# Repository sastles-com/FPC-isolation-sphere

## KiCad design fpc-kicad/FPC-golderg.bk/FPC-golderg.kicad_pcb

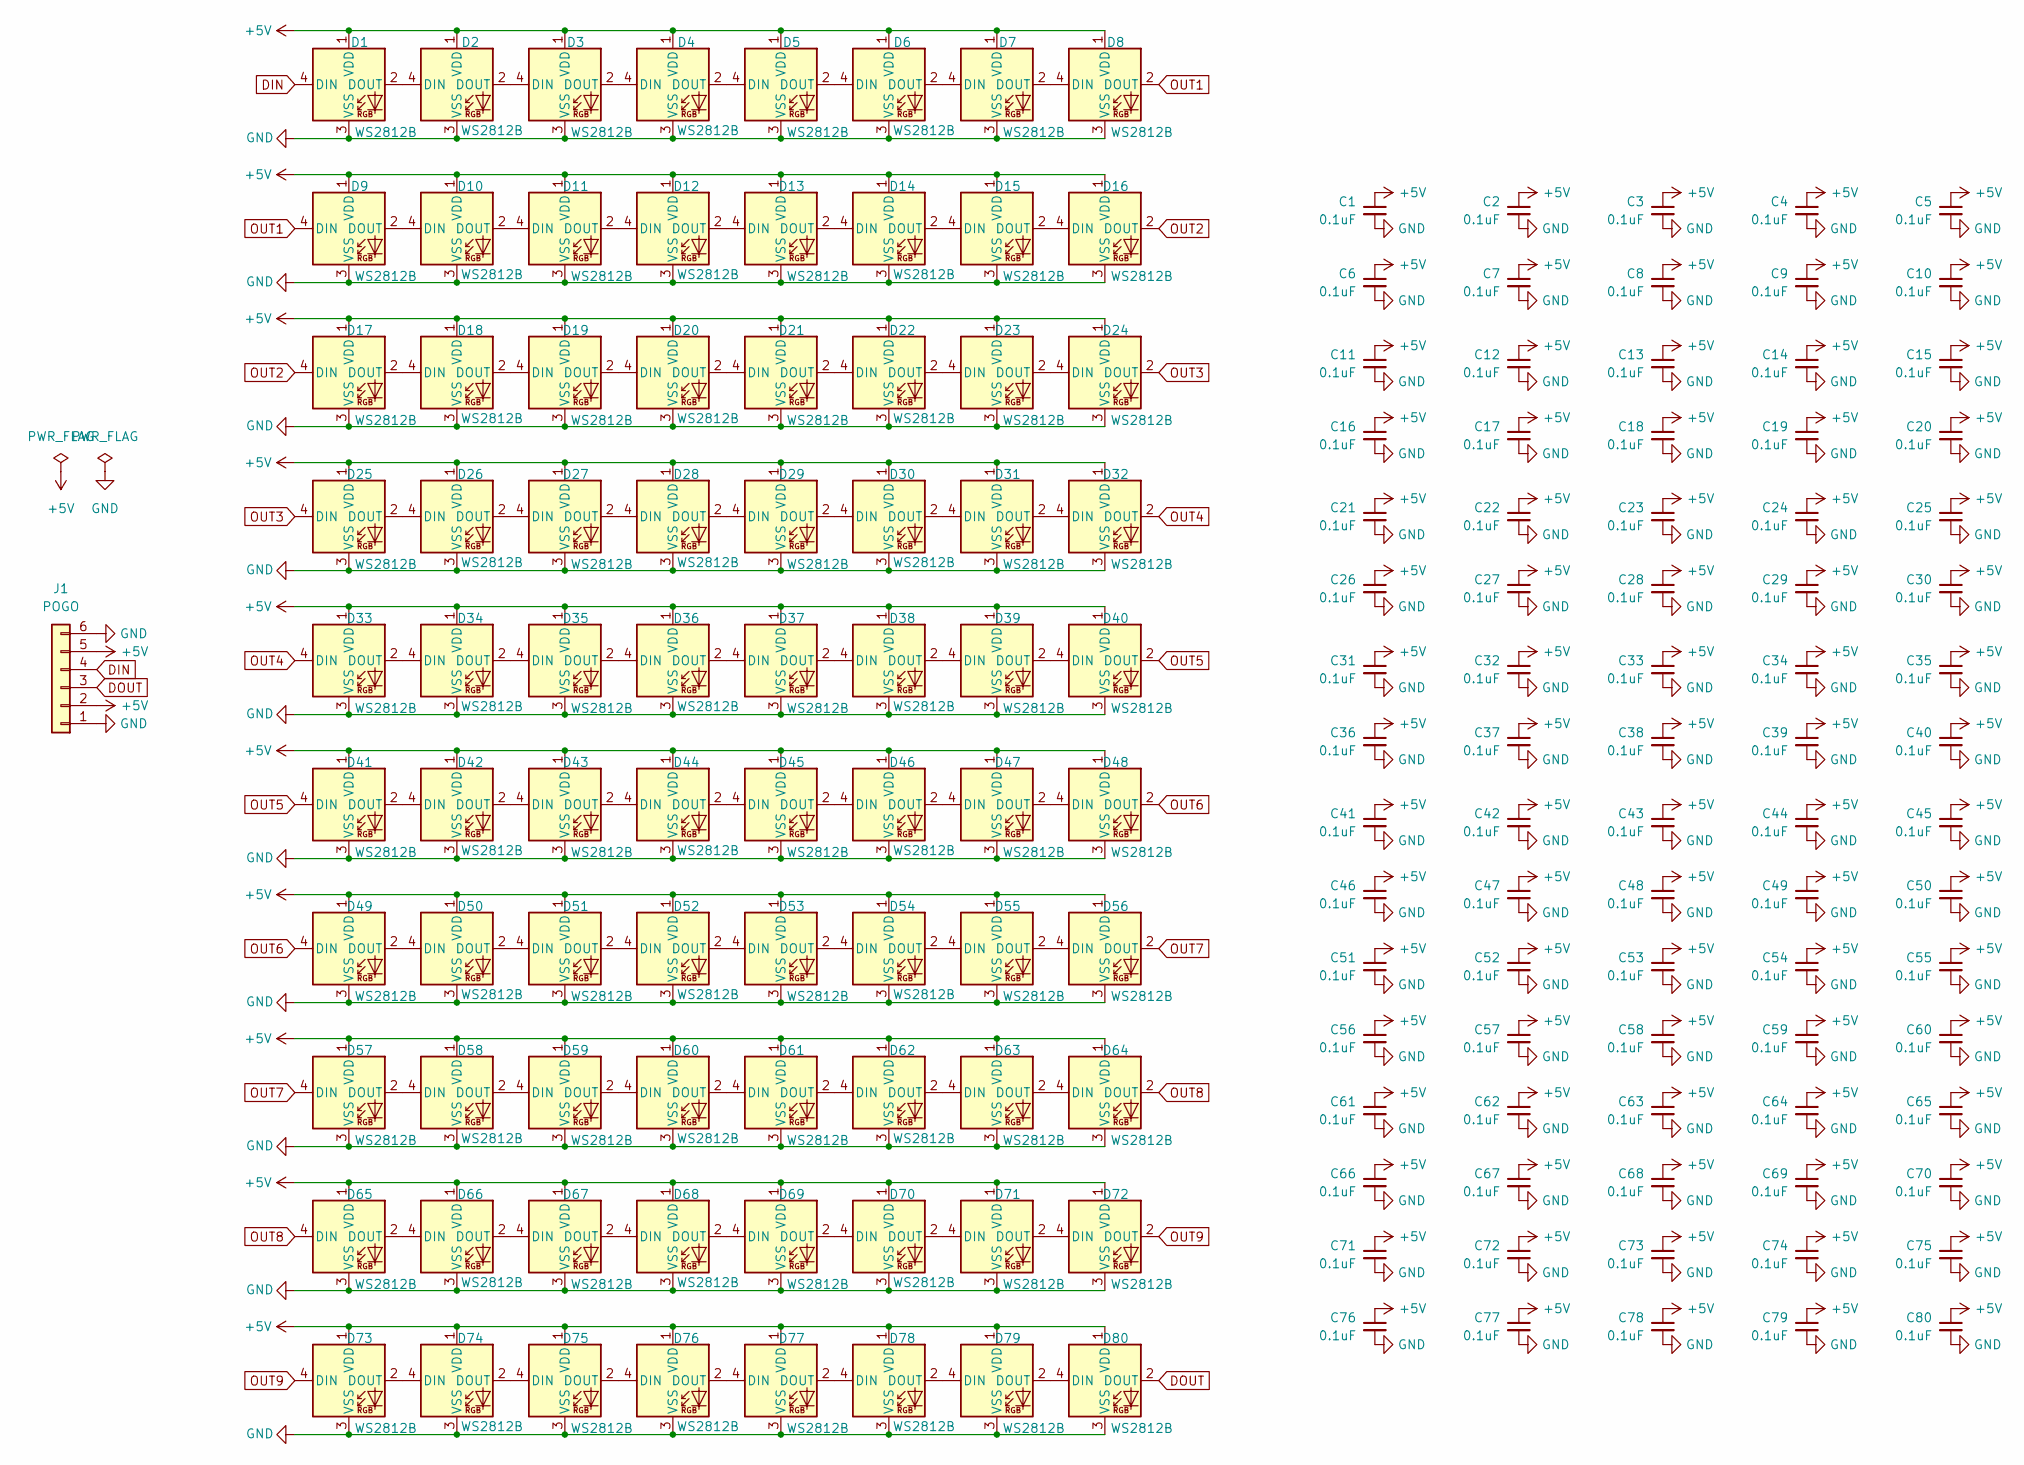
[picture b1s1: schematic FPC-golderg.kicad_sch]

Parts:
C1, C2, C3, C4, C5, C6, C7, C8, C9, C10, C11, C12, C13, C14, C15, C16, C17, C18, C19, C20, C21, C22, C23, C24, C25, C26, C27, C28, C29, C30, C31, C32, C33, C34, C35, C36, C37, C38, C39, C40, C41, C42, C43, C44, C45, C46, C47, C48, C49, C50, C51, C52, C53, C54, C55, C56, C57, C58, C59, C60, C61, C62, C63, C64, C65, C66, C67, C68, C69, C70, C71, C72, C73, C74, C75, C76, C77, C78, C79, C80: 0.1uF; C_0603_1608Metric
D1, D2, D3, D4, D5, D6, D7, D8, D9, D10, D11, D12, D13, D14, D15, D16, D17, D18, D19, D20, D21, D22, D23, D24, D25, D26, D27, D28, D29, D30, D31, D32, D33, D34, D35, D36, D37, D38, D39, D40, D41, D42, D43, D44, D45, D46, D47, D48, D49, D50, D51, D52, D53, D54, D55, D56, D57, D58, D59, D60, D61, D62, D63, D64, D65, D66, D67, D68, D69, D70, D71, D72, D73, D74, D75, D76, D77, D78, D79, D80: WS2812B; WS2812C-2020-nocut
J1: POGO; PinHeader_1x06_P2.54mm_Vertical

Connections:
+5V: C1.1, C2.1, C3.1, C4.1, C5.1, C6.1, C7.1, C8.1, C9.1, C10.1, C11.1, C12.1, C13.1, C14.1, C15.1, C16.1, C17.1, C18.1, C19.1, C20.1, C21.1, C22.1, C23.1, C24.1, C25.1, C26.1, C27.1, C28.1, C29.1, C30.1, C31.1, C32.1, C33.1, C34.1, C35.1, C36.1, C37.1, C38.1, C39.1, C40.1, C41.1, C42.1, C43.1, C44.1, C45.1, C46.1, C47.1, C48.1, C49.1, C50.1, C51.1, C52.1, C53.1, C54.1, C55.1, C56.1, C57.1, C58.1, C59.1, C60.1, C61.1, C62.1, C63.1, C64.1, C65.1, C66.1, C67.1, C68.1, C69.1, C70.1, C71.1, C72.1, C73.1, C74.1, C75.1, C76.1, C77.1, C78.1, C79.1, C80.1, D1.1 (VDD), D2.1 (VDD), D3.1 (VDD), D4.1 (VDD), D5.1 (VDD), D6.1 (VDD), D7.1 (VDD), D8.1 (VDD), D9.1 (VDD), D10.1 (VDD), D11.1 (VDD), D12.1 (VDD), D13.1 (VDD), D14.1 (VDD), D15.1 (VDD), D16.1 (VDD), D17.1 (VDD), D18.1 (VDD), D19.1 (VDD), D20.1 (VDD), D21.1 (VDD), D22.1 (VDD), D23.1 (VDD), D24.1 (VDD), D25.1 (VDD), D26.1 (VDD), D27.1 (VDD), D28.1 (VDD), D29.1 (VDD), D30.1 (VDD), D31.1 (VDD), D32.1 (VDD), D33.1 (VDD), D34.1 (VDD), D35.1 (VDD), D36.1 (VDD), D37.1 (VDD), D38.1 (VDD), D39.1 (VDD), D40.1 (VDD), D41.1 (VDD), D42.1 (VDD), D43.1 (VDD), D44.1 (VDD), D45.1 (VDD), D46.1 (VDD), D47.1 (VDD), D48.1 (VDD), D49.1 (VDD), D50.1 (VDD), D51.1 (VDD), D52.1 (VDD), D53.1 (VDD), D54.1 (VDD), D55.1 (VDD), D56.1 (VDD), D57.1 (VDD), D58.1 (VDD), D59.1 (VDD), D60.1 (VDD), D61.1 (VDD), D62.1 (VDD), D63.1 (VDD), D64.1 (VDD), D65.1 (VDD), D66.1 (VDD), D67.1 (VDD), D68.1 (VDD), D69.1 (VDD), D70.1 (VDD), D71.1 (VDD), D72.1 (VDD), D73.1 (VDD), D74.1 (VDD), D75.1 (VDD), D76.1 (VDD), D77.1 (VDD), D78.1 (VDD), D79.1 (VDD), D80.1 (VDD), J1.2, J1.5
DIN: D1.4 (DIN), J1.4
DOUT: D80.2 (DOUT), J1.3
GND: C1.2, C2.2, C3.2, C4.2, C5.2, C6.2, C7.2, C8.2, C9.2, C10.2, C11.2, C12.2, C13.2, C14.2, C15.2, C16.2, C17.2, C18.2, C19.2, C20.2, C21.2, C22.2, C23.2, C24.2, C25.2, C26.2, C27.2, C28.2, C29.2, C30.2, C31.2, C32.2, C33.2, C34.2, C35.2, C36.2, C37.2, C38.2, C39.2, C40.2, C41.2, C42.2, C43.2, C44.2, C45.2, C46.2, C47.2, C48.2, C49.2, C50.2, C51.2, C52.2, C53.2, C54.2, C55.2, C56.2, C57.2, C58.2, C59.2, C60.2, C61.2, C62.2, C63.2, C64.2, C65.2, C66.2, C67.2, C68.2, C69.2, C70.2, C71.2, C72.2, C73.2, C74.2, C75.2, C76.2, C77.2, C78.2, C79.2, C80.2, D1.3 (VSS), D2.3 (VSS), D3.3 (VSS), D4.3 (VSS), D5.3 (VSS), D6.3 (VSS), D7.3 (VSS), D8.3 (VSS), D9.3 (VSS), D10.3 (VSS), D11.3 (VSS), D12.3 (VSS), D13.3 (VSS), D14.3 (VSS), D15.3 (VSS), D16.3 (VSS), D17.3 (VSS), D18.3 (VSS), D19.3 (VSS), D20.3 (VSS), D21.3 (VSS), D22.3 (VSS), D23.3 (VSS), D24.3 (VSS), D25.3 (VSS), D26.3 (VSS), D27.3 (VSS), D28.3 (VSS), D29.3 (VSS), D30.3 (VSS), D31.3 (VSS), D32.3 (VSS), D33.3 (VSS), D34.3 (VSS), D35.3 (VSS), D36.3 (VSS), D37.3 (VSS), D38.3 (VSS), D39.3 (VSS), D40.3 (VSS), D41.3 (VSS), D42.3 (VSS), D43.3 (VSS), D44.3 (VSS), D45.3 (VSS), D46.3 (VSS), D47.3 (VSS), D48.3 (VSS), D49.3 (VSS), D50.3 (VSS), D51.3 (VSS), D52.3 (VSS), D53.3 (VSS), D54.3 (VSS), D55.3 (VSS), D56.3 (VSS), D57.3 (VSS), D58.3 (VSS), D59.3 (VSS), D60.3 (VSS), D61.3 (VSS), D62.3 (VSS), D63.3 (VSS), D64.3 (VSS), D65.3 (VSS), D66.3 (VSS), D67.3 (VSS), D68.3 (VSS), D69.3 (VSS), D70.3 (VSS), D71.3 (VSS), D72.3 (VSS), D73.3 (VSS), D74.3 (VSS), D75.3 (VSS), D76.3 (VSS), D77.3 (VSS), D78.3 (VSS), D79.3 (VSS), D80.3 (VSS), J1.1, J1.6
unnamed: D1.2 (DOUT), D2.4 (DIN)
unnamed: D2.2 (DOUT), D3.4 (DIN)
unnamed: D3.2 (DOUT), D4.4 (DIN)
unnamed: D4.2 (DOUT), D5.4 (DIN)
unnamed: D5.2 (DOUT), D6.4 (DIN)
unnamed: D6.2 (DOUT), D7.4 (DIN)
unnamed: D7.2 (DOUT), D8.4 (DIN)
unnamed: D9.2 (DOUT), D10.4 (DIN)
unnamed: D10.2 (DOUT), D11.4 (DIN)
unnamed: D11.2 (DOUT), D12.4 (DIN)
unnamed: D12.2 (DOUT), D13.4 (DIN)
unnamed: D13.2 (DOUT), D14.4 (DIN)
unnamed: D14.2 (DOUT), D15.4 (DIN)
unnamed: D15.2 (DOUT), D16.4 (DIN)
unnamed: D17.2 (DOUT), D18.4 (DIN)
unnamed: D18.2 (DOUT), D19.4 (DIN)
unnamed: D19.2 (DOUT), D20.4 (DIN)
unnamed: D20.2 (DOUT), D21.4 (DIN)
unnamed: D21.2 (DOUT), D22.4 (DIN)
unnamed: D22.2 (DOUT), D23.4 (DIN)
unnamed: D23.2 (DOUT), D24.4 (DIN)
unnamed: D25.2 (DOUT), D26.4 (DIN)
unnamed: D26.2 (DOUT), D27.4 (DIN)
unnamed: D27.2 (DOUT), D28.4 (DIN)
unnamed: D28.2 (DOUT), D29.4 (DIN)
unnamed: D29.2 (DOUT), D30.4 (DIN)
unnamed: D30.2 (DOUT), D31.4 (DIN)
unnamed: D31.2 (DOUT), D32.4 (DIN)
unnamed: D33.2 (DOUT), D34.4 (DIN)
unnamed: D34.2 (DOUT), D35.4 (DIN)
unnamed: D35.2 (DOUT), D36.4 (DIN)
unnamed: D36.2 (DOUT), D37.4 (DIN)
unnamed: D37.2 (DOUT), D38.4 (DIN)
unnamed: D38.2 (DOUT), D39.4 (DIN)
unnamed: D39.2 (DOUT), D40.4 (DIN)
unnamed: D41.2 (DOUT), D42.4 (DIN)
unnamed: D42.2 (DOUT), D43.4 (DIN)
unnamed: D43.2 (DOUT), D44.4 (DIN)
unnamed: D44.2 (DOUT), D45.4 (DIN)
unnamed: D45.2 (DOUT), D46.4 (DIN)
unnamed: D46.2 (DOUT), D47.4 (DIN)
unnamed: D47.2 (DOUT), D48.4 (DIN)
unnamed: D49.2 (DOUT), D50.4 (DIN)
unnamed: D50.2 (DOUT), D51.4 (DIN)
unnamed: D51.2 (DOUT), D52.4 (DIN)
unnamed: D52.2 (DOUT), D53.4 (DIN)
unnamed: D53.2 (DOUT), D54.4 (DIN)
unnamed: D54.2 (DOUT), D55.4 (DIN)
unnamed: D55.2 (DOUT), D56.4 (DIN)
unnamed: D57.2 (DOUT), D58.4 (DIN)
unnamed: D58.2 (DOUT), D59.4 (DIN)
unnamed: D59.2 (DOUT), D60.4 (DIN)
unnamed: D60.2 (DOUT), D61.4 (DIN)
unnamed: D61.2 (DOUT), D62.4 (DIN)
unnamed: D62.2 (DOUT), D63.4 (DIN)
unnamed: D63.2 (DOUT), D64.4 (DIN)
unnamed: D65.2 (DOUT), D66.4 (DIN)
unnamed: D66.2 (DOUT), D67.4 (DIN)
unnamed: D67.2 (DOUT), D68.4 (DIN)
unnamed: D68.2 (DOUT), D69.4 (DIN)
unnamed: D69.2 (DOUT), D70.4 (DIN)
unnamed: D70.2 (DOUT), D71.4 (DIN)
unnamed: D71.2 (DOUT), D72.4 (DIN)
unnamed: D73.2 (DOUT), D74.4 (DIN)
unnamed: D74.2 (DOUT), D75.4 (DIN)
unnamed: D75.2 (DOUT), D76.4 (DIN)
unnamed: D76.2 (DOUT), D77.4 (DIN)
unnamed: D77.2 (DOUT), D78.4 (DIN)
unnamed: D78.2 (DOUT), D79.4 (DIN)
unnamed: D79.2 (DOUT), D80.4 (DIN)
OUT1: D8.2 (DOUT), D9.4 (DIN)
OUT2: D16.2 (DOUT), D17.4 (DIN)
OUT3: D24.2 (DOUT), D25.4 (DIN)
OUT4: D32.2 (DOUT), D33.4 (DIN)
OUT5: D40.2 (DOUT), D41.4 (DIN)
OUT6: D48.2 (DOUT), D49.4 (DIN)
OUT7: D56.2 (DOUT), D57.4 (DIN)
OUT8: D64.2 (DOUT), D65.4 (DIN)
OUT9: D72.2 (DOUT), D73.4 (DIN)

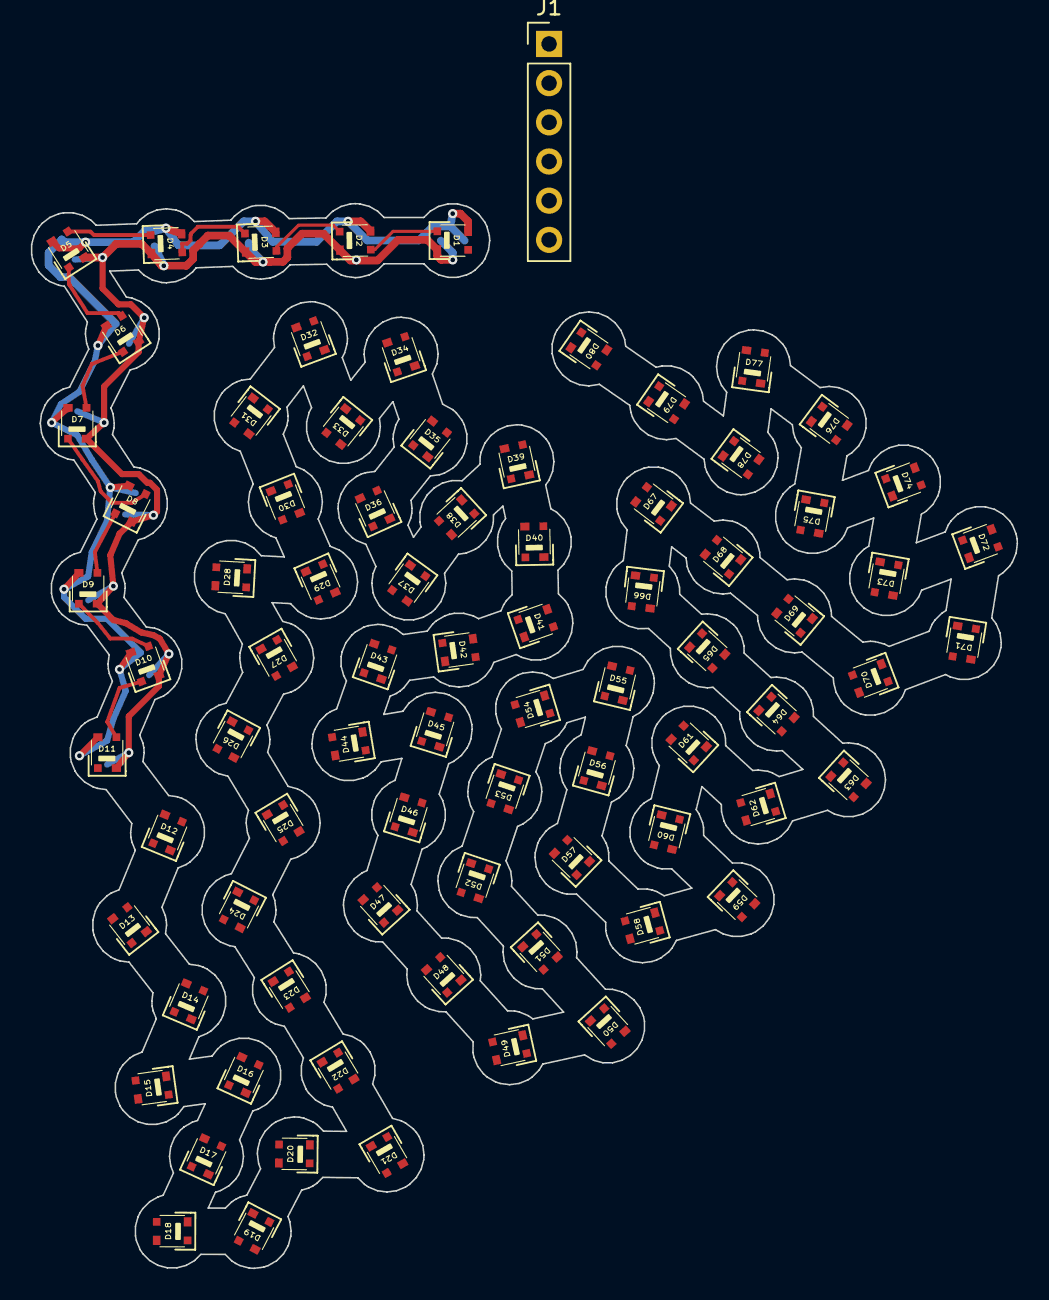
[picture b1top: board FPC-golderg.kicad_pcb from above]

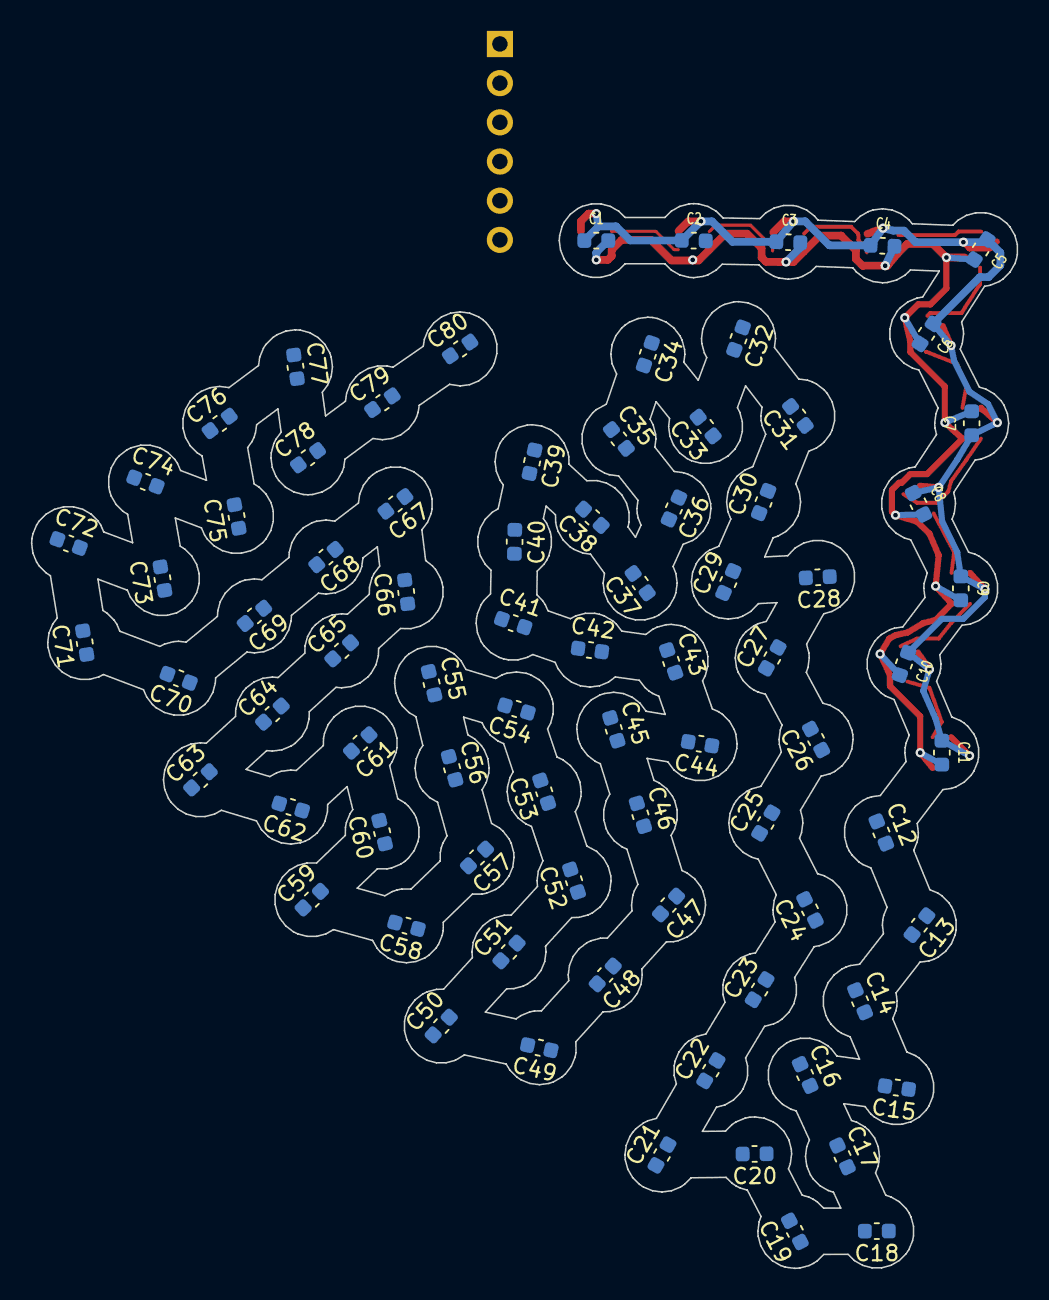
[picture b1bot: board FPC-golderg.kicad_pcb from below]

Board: 2 copper layers, 63.9 x 69.0 mm, 161 parts (80 on the bottom side), 83 nets.

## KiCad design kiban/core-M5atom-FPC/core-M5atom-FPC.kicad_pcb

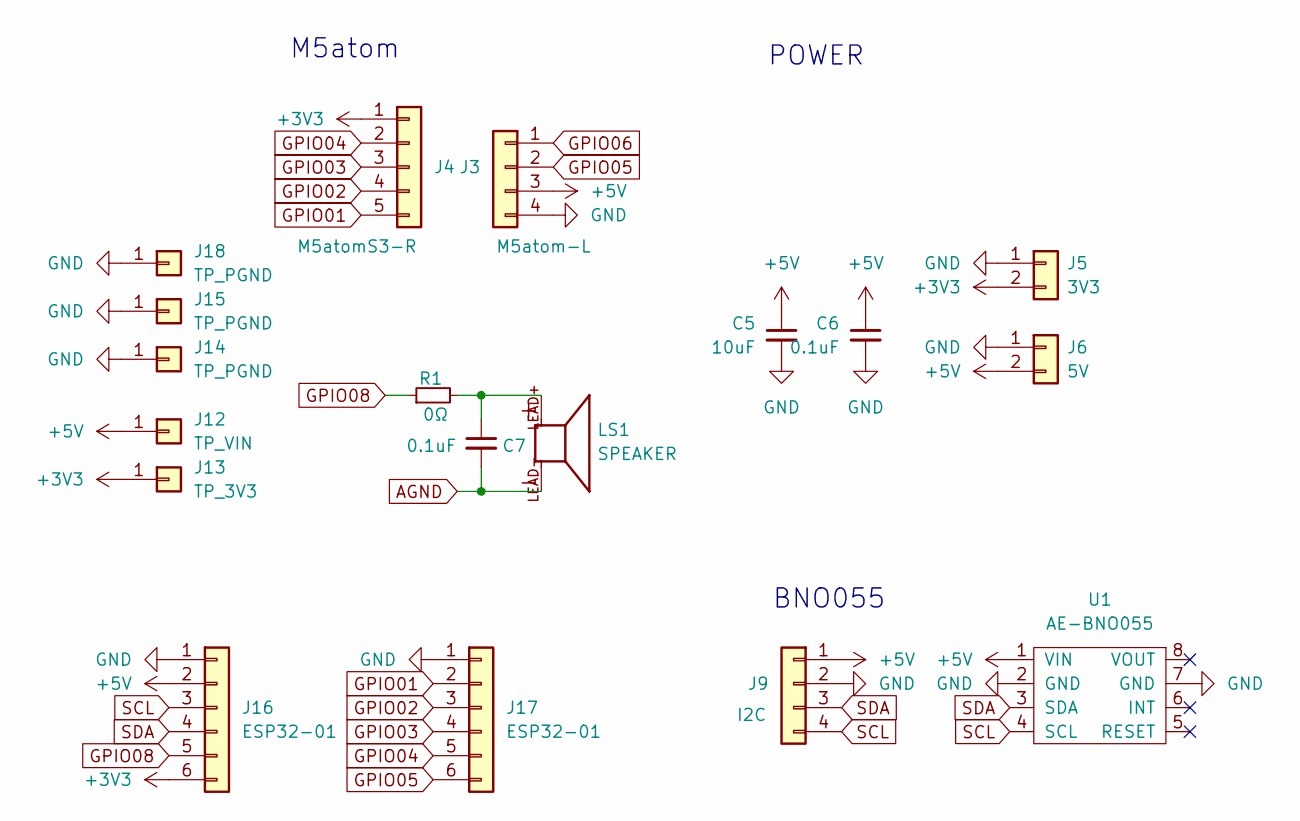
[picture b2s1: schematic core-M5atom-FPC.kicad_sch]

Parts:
C5: 10uF; C_0603_1608Metric_Pad1.08x0.95mm_HandSolder
C6, C7: 0.1uF; C_0603_1608Metric_Pad1.08x0.95mm_HandSolder
J3: M5atom-L; PinHeader_1x04_P2.54mm_Vertical_SMD_Pin1Left
J4: M5atomS3-R; PinHeader_1x05_P2.54mm_Vertical_SMD_Pin1Left
J5: 3V3; PinHeader_1x02_P2.00mm_Vertical
J6: 5V; PinHeader_1x02_P2.00mm_Vertical
J9: I2C; PinHeader_1x04_P2.00mm_Vertical
J12: TP_VIN; PinHeader_1x01_P2.54mm_Vertical
J13: TP_3V3; PinHeader_1x01_P2.54mm_Vertical
J14, J15, J18: TP_PGND; PinHeader_1x01_P2.54mm_Vertical
J16, J17: ESP32-01; PinHeader_1x06_P2.54mm_Vertical
LS1: SPEAKER; speaker-PKLCS1212; PARTREV C
R1: 0Ω; C_0603_1608Metric
U1: AE-BNO055; AE-BNO055-nohole

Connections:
+3V3: J4.1, J5.2, J13.1 (Pin_1_1), J16.6
+5V: C5.1, C6.1, J3.3, J6.2, J9.1, J12.1 (Pin_1_1), J16.2, U1.1 (VIN)
AGND: C7.2, LS1.LEAD-
GND: C5.2, C6.2, J3.4, J5.1, J6.1, J9.2, J14.1 (Pin_1_1), J15.1 (Pin_1_1), J16.1, J17.1, J18.1 (Pin_1_1), U1.2 (GND), U1.7 (GND)
GPIO01: J4.5, J17.2
GPIO02: J4.4, J17.3
GPIO03: J4.3, J17.4
GPIO04: J4.2, J17.5
GPIO05: J3.2, J17.6
GPIO06: J3.1
GPIO08: J16.5, R1.1
unnamed: C7.1, LS1.LEAD+, R1.2
SCL: J9.4, J16.3, U1.4 (SCL)
SDA: J9.3, J16.4, U1.3 (SDA)

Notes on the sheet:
M5atom
BNO055
POWER

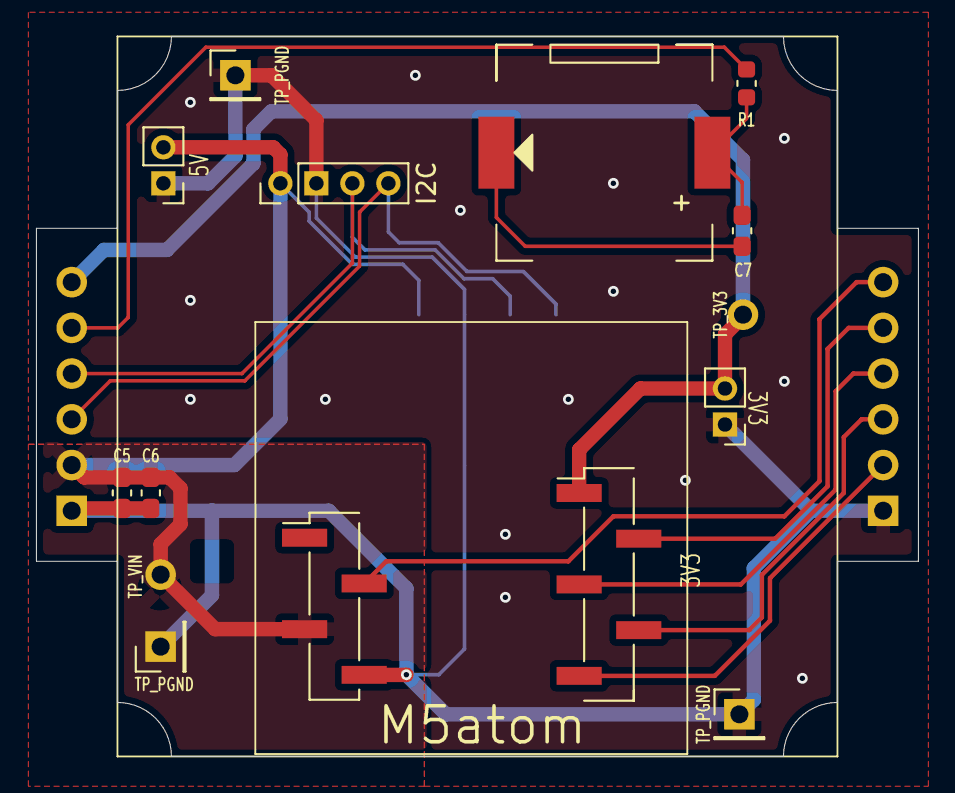
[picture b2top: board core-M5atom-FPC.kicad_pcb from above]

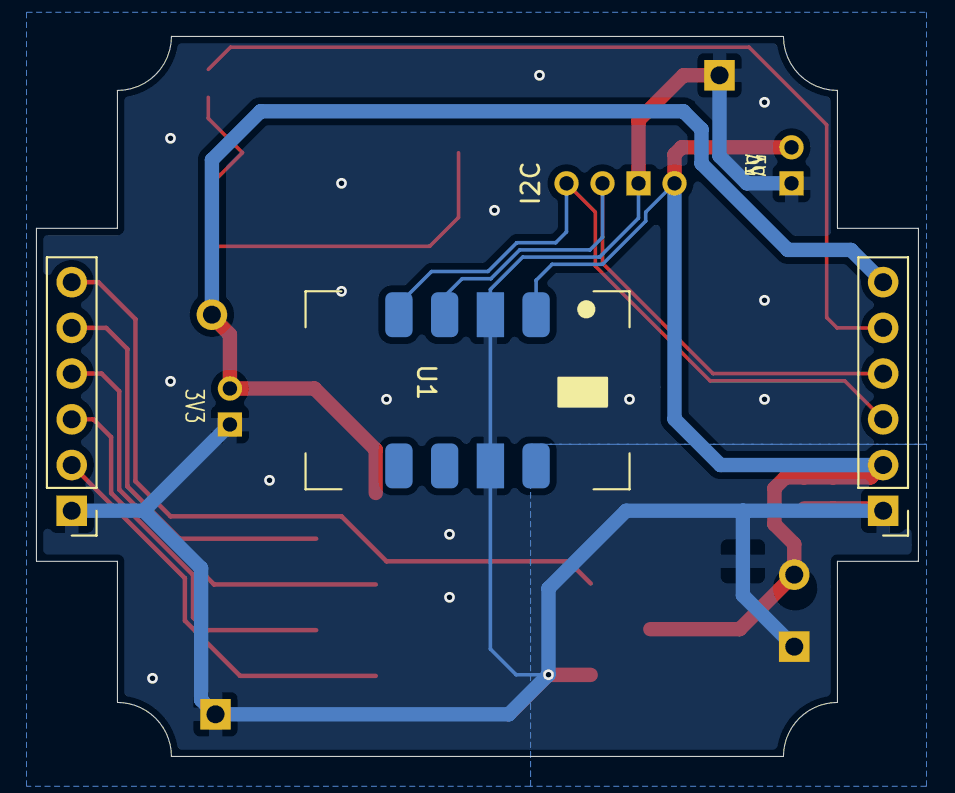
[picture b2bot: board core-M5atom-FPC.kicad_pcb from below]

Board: 2 copper layers, 49.0 x 40.0 mm, 18 parts (3 on the bottom side), 13 nets.
